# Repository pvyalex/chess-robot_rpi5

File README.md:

# chess-robot_rpi5

Chess-playing robot arm project using a Raspberry Pi 5 for vision/logic and an ESP32 for servo control.

## What this repo contains
- `main/rpi5/`: Python code for vision, move detection, and robot control.
- `main/esp32/`: ESP32 firmware for servo motion and gripper control.
- `yolo26n/`: Trained segmentation model and dataset artifacts.
- `pcb/`: KiCad files for hardware.
- `robot_arm/`: 3D model and calibration sketch.

## High-level flow
1. Capture a reference board image and calibrate perspective.
2. Detect the human move by comparing new frames to the reference.
3. Compute the engine reply and command the robot arm to move the piece.

## Run (Raspberry Pi 5)
Open [main/rpi5/main.py](main/rpi5/main.py) and run it from that folder. The script:
- captures images,
- detects the move,
- asks the chess engine for a reply,
- and drives the robot arm over UART.

If your ESP32 is on a different serial port than `COM3`, update the port passed to `ChessRobot` in [main/rpi5/main.py](main/rpi5/main.py).

## ESP32 firmware
Upload [main/esp32/esp32_source.ino](main/esp32/esp32_source.ino) to the ESP32. It expects servo pins defined at the top of the file and listens for commands from the host.

## Notes
- The vision pipeline uses the model under `yolo26n/model/` for calibration and detection.
- Movement logic and inverse kinematics are implemented in [main/rpi5/chess_robot_ik_only.py](main/rpi5/chess_robot_ik_only.py).

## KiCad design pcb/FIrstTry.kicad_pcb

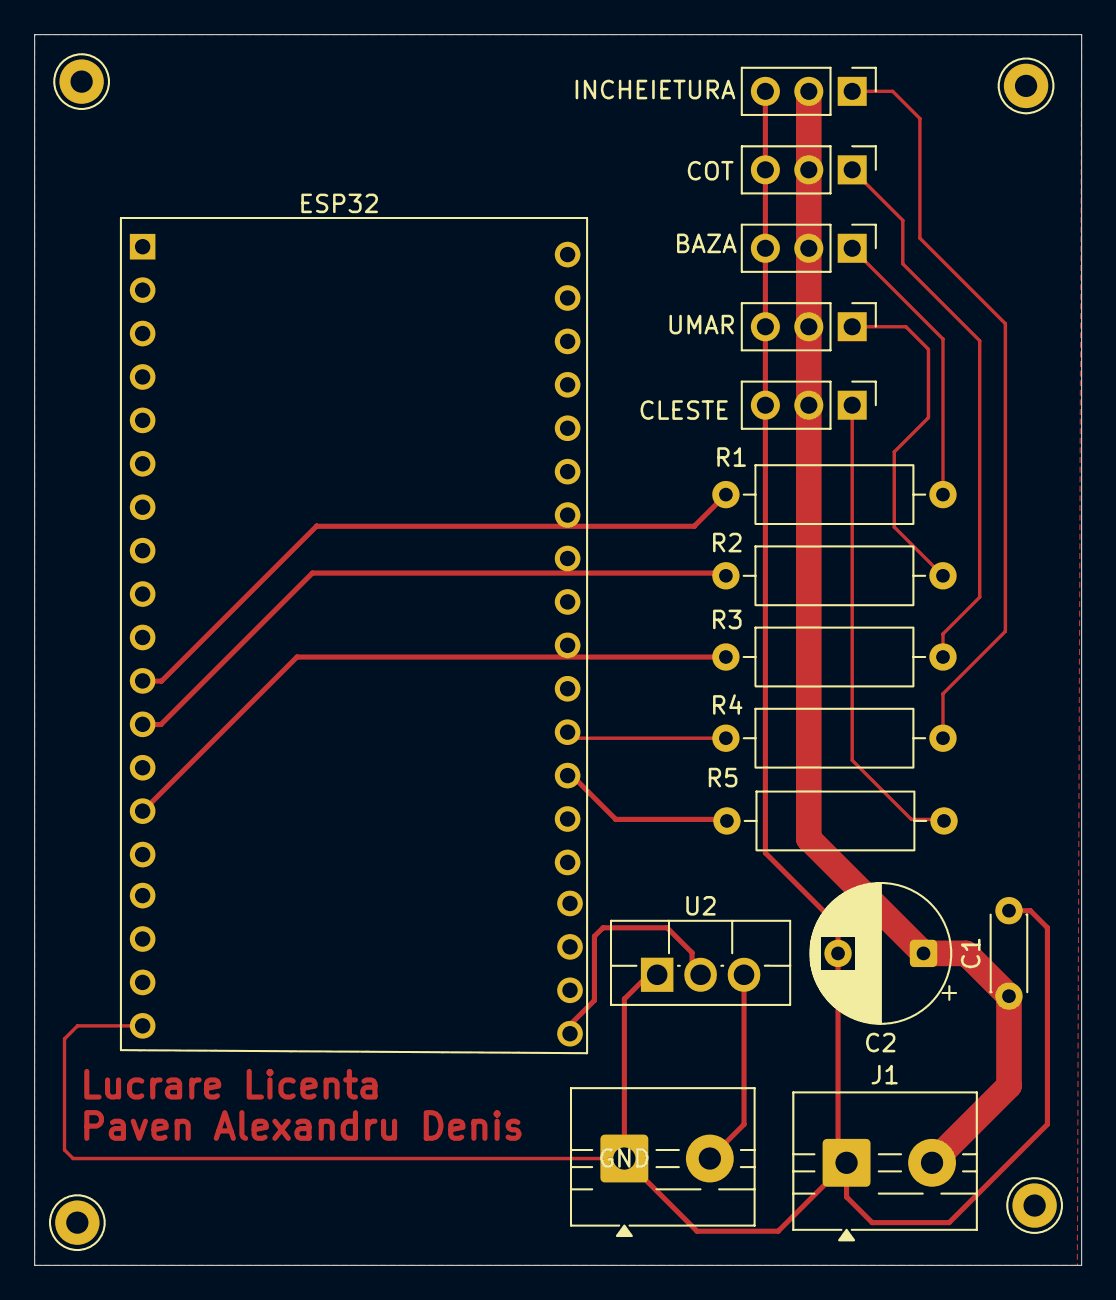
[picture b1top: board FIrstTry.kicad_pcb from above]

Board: 2 copper layers, 61.2 x 72.0 mm, 16 parts (0 on the bottom side), 16 nets.

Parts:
C1: C; C_Disc_D4.3mm_W1.9mm_P5.00mm
C2: C_Polarized; CP_Radial_D8.0mm_P5.00mm
ESP32: ESP32-C3-DevKitM-1_38pins; ESP32-C3-DevKitM-1
J1, J2: Screw_Terminal_01x02; TerminalBlock_MaiXu_MX126-5.0-02P_1x02_P5.00mm
M2, M3, M4, M5, M11: Motor_Servo; PinHeader_1x03_P2.54mm_Vertical
R1, R2, R3, R4, R5: R; R_Axial_DIN0309_L9.0mm_D3.2mm_P12.70mm_Horizontal
U2: LM1085-3.3; TO-220F-3_Vertical

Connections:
+3V3: ESP32.20 (IO4), U2.2 (VO)
+5V: C1.1, C2.1, J1.2, M2.2 (+), M3.2 (+), M4.2 (+), M5.2 (+), M11.2 (+)
GND: C1.2, C2.2, ESP32.19 (IO20), J1.1, J2.1, M2.3 (-), M3.3 (-), M4.3 (-), M5.3 (-), M11.3 (-), U2.1 (GND)
unnamed: J2.2, U2.3 (VI)
unnamed: M2.1 (PWM), R4.2
unnamed: M3.1 (PWM), R3.2
unnamed: M4.1 (PWM), R1.2
unnamed: M5.1 (PWM), R2.2
unnamed: M11.1 (PWM), R5.2
unnamed: ESP32.12 (IO29), R2.1
unnamed: ESP32.27 (IO20), R4.1
unnamed: ESP32.2 (3V3), ESP32.3 (3V3)
unnamed: ESP32.26 (IO9), R5.1
unnamed: ESP32.11 (IO10), R1.1
unnamed: ESP32.14 (IO30), R3.1
unnamed: ESP32.1, ESP32.6, ESP32.8, ESP32.15, ESP32.16, ESP32.24, ESP32.30

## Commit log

2026-05-10 readme
2026-05-12 Add arc-based movement traversal
    Agent-Logs-Url: https://github.com/pvyalex/chess-robot_rpi5/sessions/61b41980-4d08-48c4-92c1-48ab55fd229c
2026-05-12 Define waypoint delay constant
    Agent-Logs-Url: https://github.com/pvyalex/chess-robot_rpi5/sessions/61b41980-4d08-48c4-92c1-48ab55fd229c
2026-05-12 Speed up ESP32 motion ramp and smooth shoulder entry
    Agent-Logs-Url: https://github.com/pvyalex/chess-robot_rpi5/sessions/89bc9969-a6c0-406a-8d58-64ae14d89013
2026-05-12 Clarify shoulder entry move parameters
    Agent-Logs-Url: https://github.com/pvyalex/chess-robot_rpi5/sessions/89bc9969-a6c0-406a-8d58-64ae14d89013
2026-05-13 offset regulations
